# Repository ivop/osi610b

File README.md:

# Ohio Scientific 610B Remake

### Remake of the Ohio Scientific 610B Floppy Controller and Memory Expansion PCB

* The new [schematics](doc/osi610b-schematic.pdf) are based on the original schematics, but with all [errors](doc/errors.txt) fixed.
* The PCB is mostly identical to the original, but with added silkscreen, and jumpers instead of trace cuts.
* Except for drive type selection, which is kept original and does not have a solder mask to facilitate original adjustments.
* Use [ramtest2114](https://github.com/ivop/ramtest2114) to test RAM chips acquired from Ali.

Can be paired with the [Ohio Scientific 600D](https://github.com/ivop/osi600d) "CPU" board.

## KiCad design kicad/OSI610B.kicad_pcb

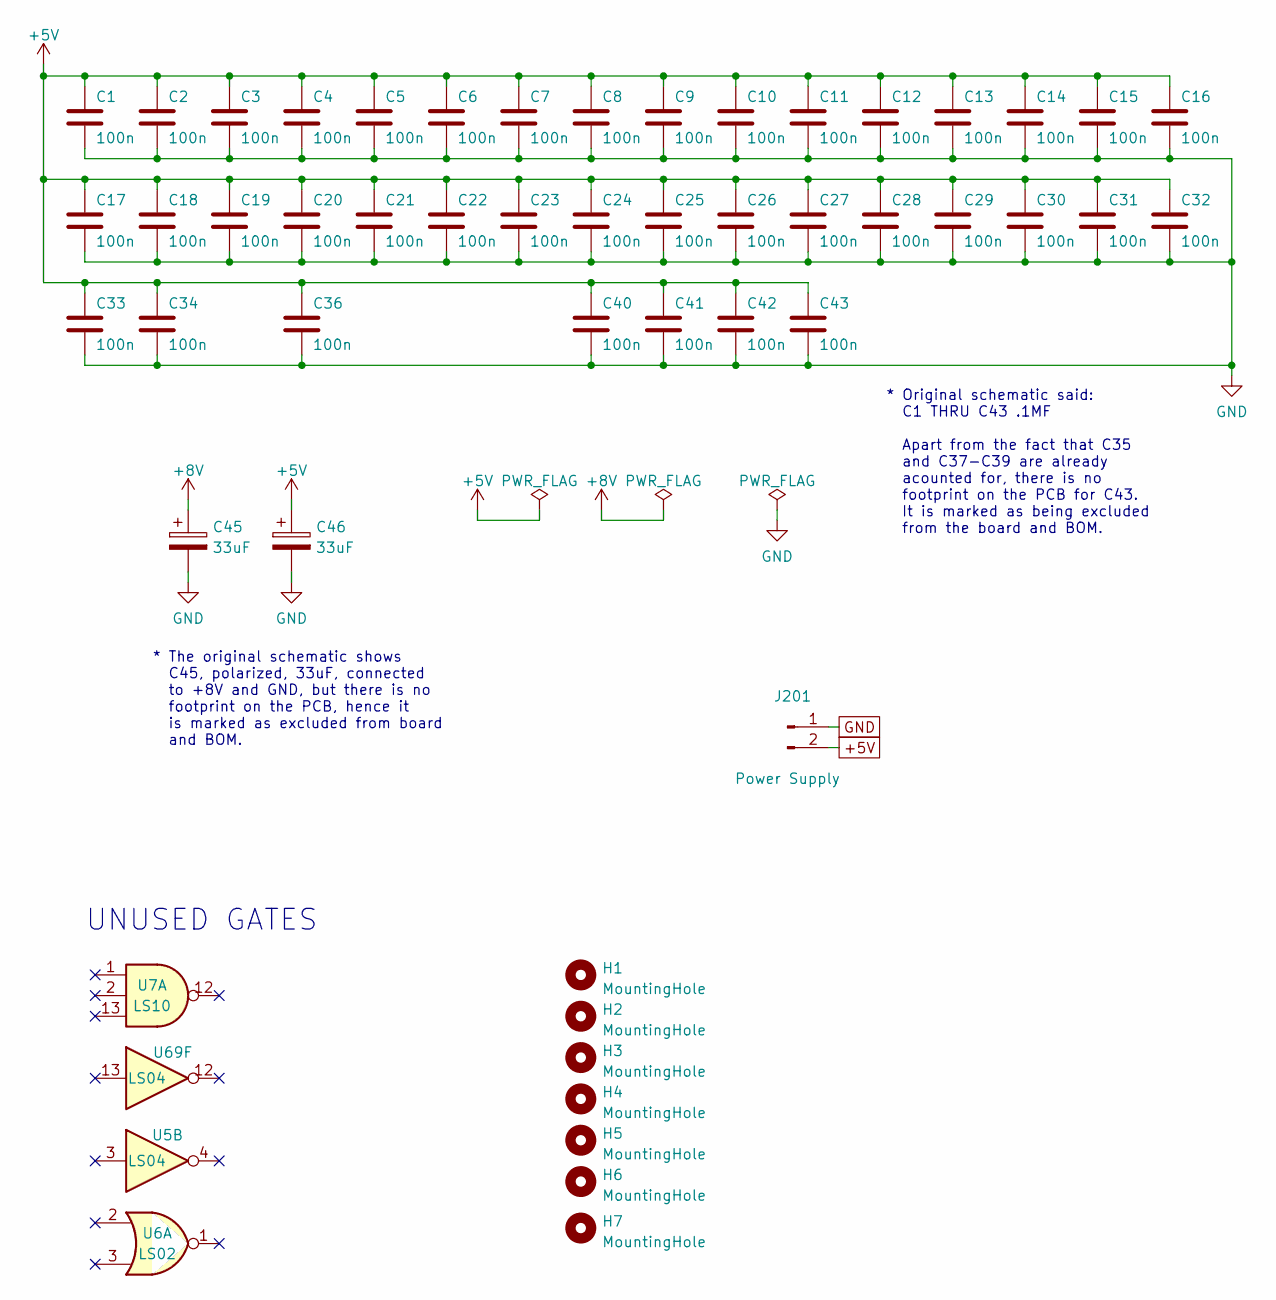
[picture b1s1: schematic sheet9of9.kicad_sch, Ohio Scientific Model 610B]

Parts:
C1, C2, C3, C4, C5, C6, C7, C8, C9, C10, C11, C12, C13, C14, C15, C16, C17, C18, C19, C20, C21, C22, C23, C24, C25, C26, C27, C28, C29, C30, C31, C32, C33, C34, C36, C40, C41, C42, C43: 100n; C_Disc_D4.3mm_W1.9mm_P5.00mm
C45: 33uF
C46: 33uF; CP_Axial_L11.0mm_D6.0mm_P18.00mm_Horizontal
H1, H2, H3, H4, H5: MountingHole; MountingHole_4.3mm_M4_ISO14580
H6, H7: MountingHole; MountingHole_2.7mm_M2.5_ISO14580
J201: Power Supply; Molex_KK-396_A-41791-0002_1x02_P3.96mm_Vertical
U5, U69: LS04; DIP-14_W7.62mm_Socket_LongPads
U6: LS02; DIP-14_W7.62mm_Socket_LongPads
U7: LS10; DIP-14_W7.62mm_Socket_LongPads

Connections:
+5V: C1.1, C2.1, C3.1, C4.1, C5.1, C6.1, C7.1, C8.1, C9.1, C10.1, C11.1, C12.1, C13.1, C14.1, C15.1, C16.1, C17.1, C18.1, C19.1, C20.1, C21.1, C22.1, C23.1, C24.1, C25.1, C26.1, C27.1, C28.1, C29.1, C30.1, C31.1, C32.1, C33.1, C34.1, C36.1, C40.1, C41.1, C42.1, C43.1, C46.1, J201.2; also elsewhere on the board
GND: C1.2, C2.2, C3.2, C4.2, C5.2, C6.2, C7.2, C8.2, C9.2, C10.2, C11.2, C12.2, C13.2, C14.2, C15.2, C16.2, C17.2, C18.2, C19.2, C20.2, C21.2, C22.2, C23.2, C24.2, C25.2, C26.2, C27.2, C28.2, C29.2, C30.2, C31.2, C32.2, C33.2, C34.2, C36.2, C40.2, C41.2, C42.2, C43.2, C45.2, C46.2, J201.1; also elsewhere on the board

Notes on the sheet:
UNUSED GATES
* Original schematic said: C1 THRU C43 .1MF Apart from the fact that C35 and C37-C39 are already acounted for, there is no footprint on the PCB for C43. It is marked as being excluded from the board and BOM.
* The original schematic shows C45, polarized, 33uF, connected to +8V and GND, but there is no footprint on the PCB, hence it is marked as excluded from board and BOM.

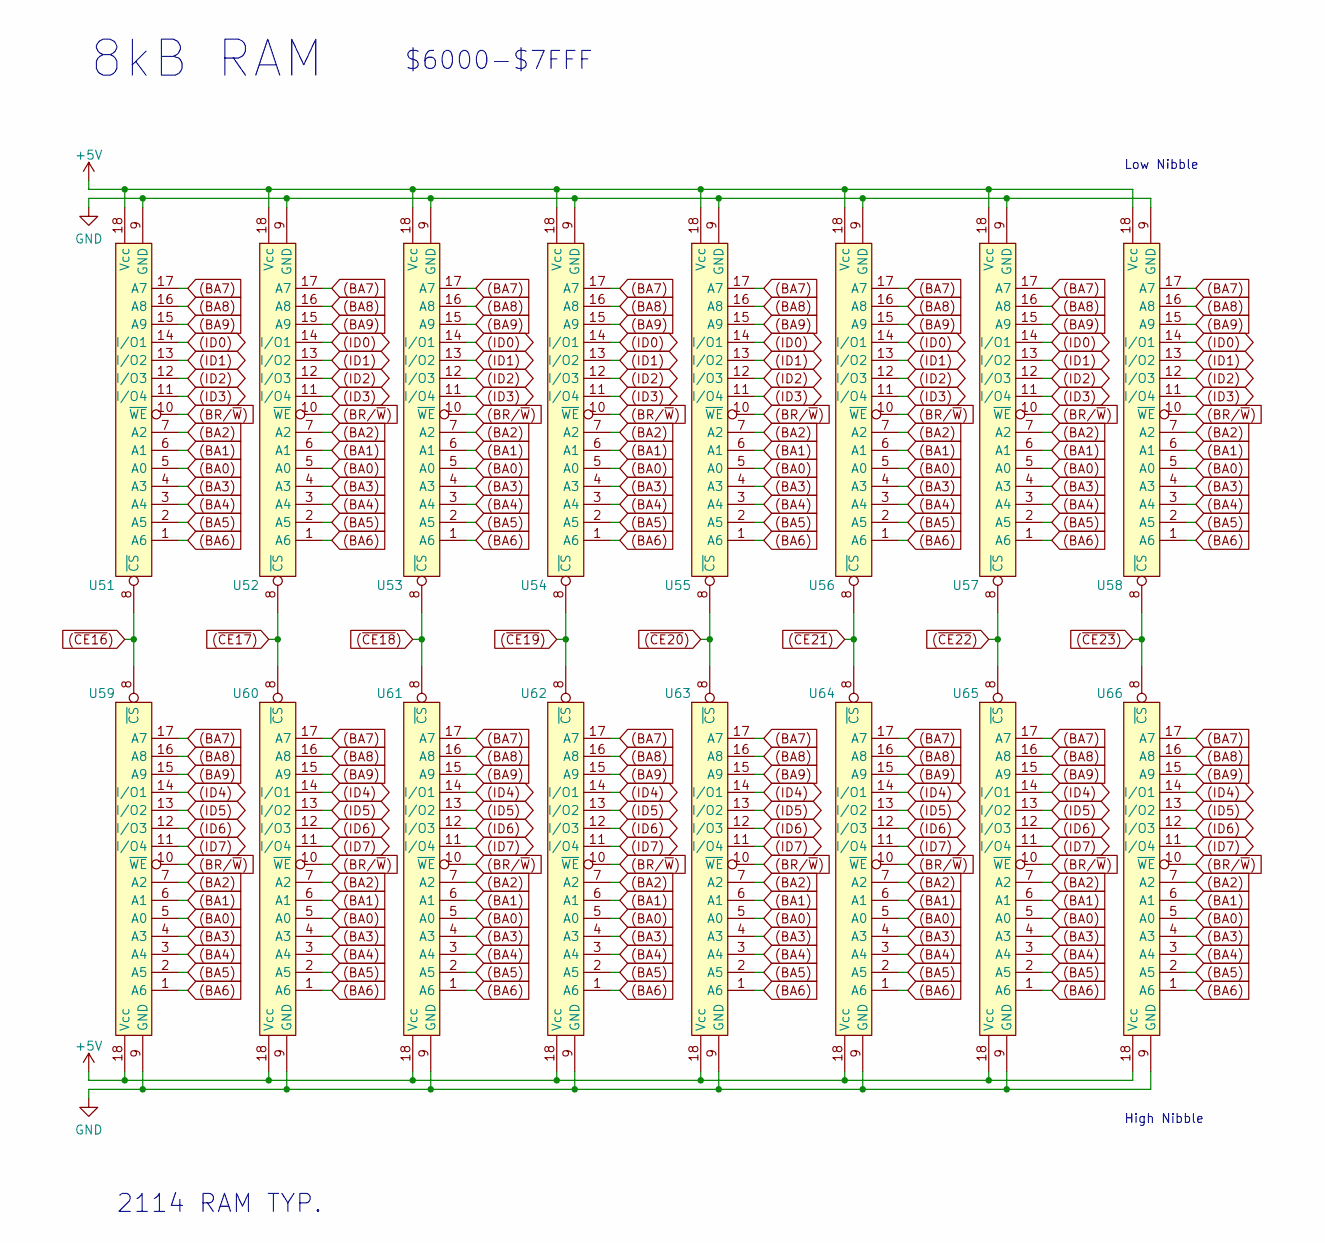
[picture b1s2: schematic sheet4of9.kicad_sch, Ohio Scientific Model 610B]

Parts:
U51, U52, U53, U54, U55, U56, U57, U58: 2114_CS_BOTTOM; DIP-18_W7.62mm_Socket_LongPads
U59, U60, U61, U62, U63, U64, U65, U66: 2114 CS TOP; DIP-18_W7.62mm_Socket_LongPads

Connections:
(BA0): U51.5 (A0), U52.5 (A0), U53.5 (A0), U54.5 (A0), U55.5 (A0), U56.5 (A0), U57.5 (A0), U58.5 (A0), U59.5 (A0), U60.5 (A0), U61.5 (A0), U62.5 (A0), U63.5 (A0), U64.5 (A0), U65.5 (A0), U66.5 (A0); also elsewhere on the board
(BA1): U51.6 (A1), U52.6 (A1), U53.6 (A1), U54.6 (A1), U55.6 (A1), U56.6 (A1), U57.6 (A1), U58.6 (A1), U59.6 (A1), U60.6 (A1), U61.6 (A1), U62.6 (A1), U63.6 (A1), U64.6 (A1), U65.6 (A1), U66.6 (A1); also elsewhere on the board
(BA2): U51.7 (A2), U52.7 (A2), U53.7 (A2), U54.7 (A2), U55.7 (A2), U56.7 (A2), U57.7 (A2), U58.7 (A2), U59.7 (A2), U60.7 (A2), U61.7 (A2), U62.7 (A2), U63.7 (A2), U64.7 (A2), U65.7 (A2), U66.7 (A2); also elsewhere on the board
(BA3): U51.4 (A3), U52.4 (A3), U53.4 (A3), U54.4 (A3), U55.4 (A3), U56.4 (A3), U57.4 (A3), U58.4 (A3), U59.4 (A3), U60.4 (A3), U61.4 (A3), U62.4 (A3), U63.4 (A3), U64.4 (A3), U65.4 (A3), U66.4 (A3); also elsewhere on the board
(BA4): U51.3 (A4), U52.3 (A4), U53.3 (A4), U54.3 (A4), U55.3 (A4), U56.3 (A4), U57.3 (A4), U58.3 (A4), U59.3 (A4), U60.3 (A4), U61.3 (A4), U62.3 (A4), U63.3 (A4), U64.3 (A4), U65.3 (A4), U66.3 (A4); also elsewhere on the board
(BA5): U51.2 (A5), U52.2 (A5), U53.2 (A5), U54.2 (A5), U55.2 (A5), U56.2 (A5), U57.2 (A5), U58.2 (A5), U59.2 (A5), U60.2 (A5), U61.2 (A5), U62.2 (A5), U63.2 (A5), U64.2 (A5), U65.2 (A5), U66.2 (A5); also elsewhere on the board
(BA6): U51.1 (A6), U52.1 (A6), U53.1 (A6), U54.1 (A6), U55.1 (A6), U56.1 (A6), U57.1 (A6), U58.1 (A6), U59.1 (A6), U60.1 (A6), U61.1 (A6), U62.1 (A6), U63.1 (A6), U64.1 (A6), U65.1 (A6), U66.1 (A6); also elsewhere on the board
(BA7): U51.17 (A7), U52.17 (A7), U53.17 (A7), U54.17 (A7), U55.17 (A7), U56.17 (A7), U57.17 (A7), U58.17 (A7), U59.17 (A7), U60.17 (A7), U61.17 (A7), U62.17 (A7), U63.17 (A7), U64.17 (A7), U65.17 (A7), U66.17 (A7); also elsewhere on the board
(BA8): U51.16 (A8), U52.16 (A8), U53.16 (A8), U54.16 (A8), U55.16 (A8), U56.16 (A8), U57.16 (A8), U58.16 (A8), U59.16 (A8), U60.16 (A8), U61.16 (A8), U62.16 (A8), U63.16 (A8), U64.16 (A8), U65.16 (A8), U66.16 (A8); also elsewhere on the board
(BA9): U51.15 (A9), U52.15 (A9), U53.15 (A9), U54.15 (A9), U55.15 (A9), U56.15 (A9), U57.15 (A9), U58.15 (A9), U59.15 (A9), U60.15 (A9), U61.15 (A9), U62.15 (A9), U63.15 (A9), U64.15 (A9), U65.15 (A9), U66.15 (A9); also elsewhere on the board
(BR/~W): U51.10 (~WE), U52.10 (~WE), U53.10 (~WE), U54.10 (~WE), U55.10 (~WE), U56.10 (~WE), U57.10 (~WE), U58.10 (~WE), U59.10 (~WE), U60.10 (~WE), U61.10 (~WE), U62.10 (~WE), U63.10 (~WE), U64.10 (~WE), U65.10 (~WE), U66.10 (~WE); also elsewhere on the board
(ID0): U51.14 (I/O1), U52.14 (I/O1), U53.14 (I/O1), U54.14 (I/O1), U55.14 (I/O1), U56.14 (I/O1), U57.14 (I/O1), U58.14 (I/O1); also elsewhere on the board
(ID1): U51.13 (I/O2), U52.13 (I/O2), U53.13 (I/O2), U54.13 (I/O2), U55.13 (I/O2), U56.13 (I/O2), U57.13 (I/O2), U58.13 (I/O2); also elsewhere on the board
(ID2): U51.12 (I/O3), U52.12 (I/O3), U53.12 (I/O3), U54.12 (I/O3), U55.12 (I/O3), U56.12 (I/O3), U57.12 (I/O3), U58.12 (I/O3); also elsewhere on the board
(ID3): U51.11 (I/O4), U52.11 (I/O4), U53.11 (I/O4), U54.11 (I/O4), U55.11 (I/O4), U56.11 (I/O4), U57.11 (I/O4), U58.11 (I/O4); also elsewhere on the board
(ID4): U59.14 (I/O1), U60.14 (I/O1), U61.14 (I/O1), U62.14 (I/O1), U63.14 (I/O1), U64.14 (I/O1), U65.14 (I/O1), U66.14 (I/O1); also elsewhere on the board
(ID5): U59.13 (I/O2), U60.13 (I/O2), U61.13 (I/O2), U62.13 (I/O2), U63.13 (I/O2), U64.13 (I/O2), U65.13 (I/O2), U66.13 (I/O2); also elsewhere on the board
(ID6): U59.12 (I/O3), U60.12 (I/O3), U61.12 (I/O3), U62.12 (I/O3), U63.12 (I/O3), U64.12 (I/O3), U65.12 (I/O3), U66.12 (I/O3); also elsewhere on the board
(ID7): U59.11 (I/O4), U60.11 (I/O4), U61.11 (I/O4), U62.11 (I/O4), U63.11 (I/O4), U64.11 (I/O4), U65.11 (I/O4), U66.11 (I/O4); also elsewhere on the board
(~CE16): U51.8 (~CS), U59.8 (~CS); also elsewhere on the board
(~CE17): U52.8 (~CS), U60.8 (~CS); also elsewhere on the board
(~CE18): U53.8 (~CS), U61.8 (~CS); also elsewhere on the board
(~CE19): U54.8 (~CS), U62.8 (~CS); also elsewhere on the board
(~CE20): U55.8 (~CS), U63.8 (~CS); also elsewhere on the board
(~CE21): U56.8 (~CS), U64.8 (~CS); also elsewhere on the board
(~CE22): U57.8 (~CS), U65.8 (~CS); also elsewhere on the board
(~CE23): U58.8 (~CS), U66.8 (~CS); also elsewhere on the board
+5V: U51.18 (Vcc), U52.18 (Vcc), U53.18 (Vcc), U54.18 (Vcc), U55.18 (Vcc), U56.18 (Vcc), U57.18 (Vcc), U58.18 (Vcc), U59.18 (Vcc), U60.18 (Vcc), U61.18 (Vcc), U62.18 (Vcc), U63.18 (Vcc), U64.18 (Vcc), U65.18 (Vcc), U66.18 (Vcc); also elsewhere on the board
GND: U51.9 (GND), U52.9 (GND), U53.9 (GND), U54.9 (GND), U55.9 (GND), U56.9 (GND), U57.9 (GND), U58.9 (GND), U59.9 (GND), U60.9 (GND), U61.9 (GND), U62.9 (GND), U63.9 (GND), U64.9 (GND), U65.9 (GND), U66.9 (GND); also elsewhere on the board

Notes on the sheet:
2114 RAM TYP.
8kB RAM
High Nibble
$6000-$7FFF
Low Nibble

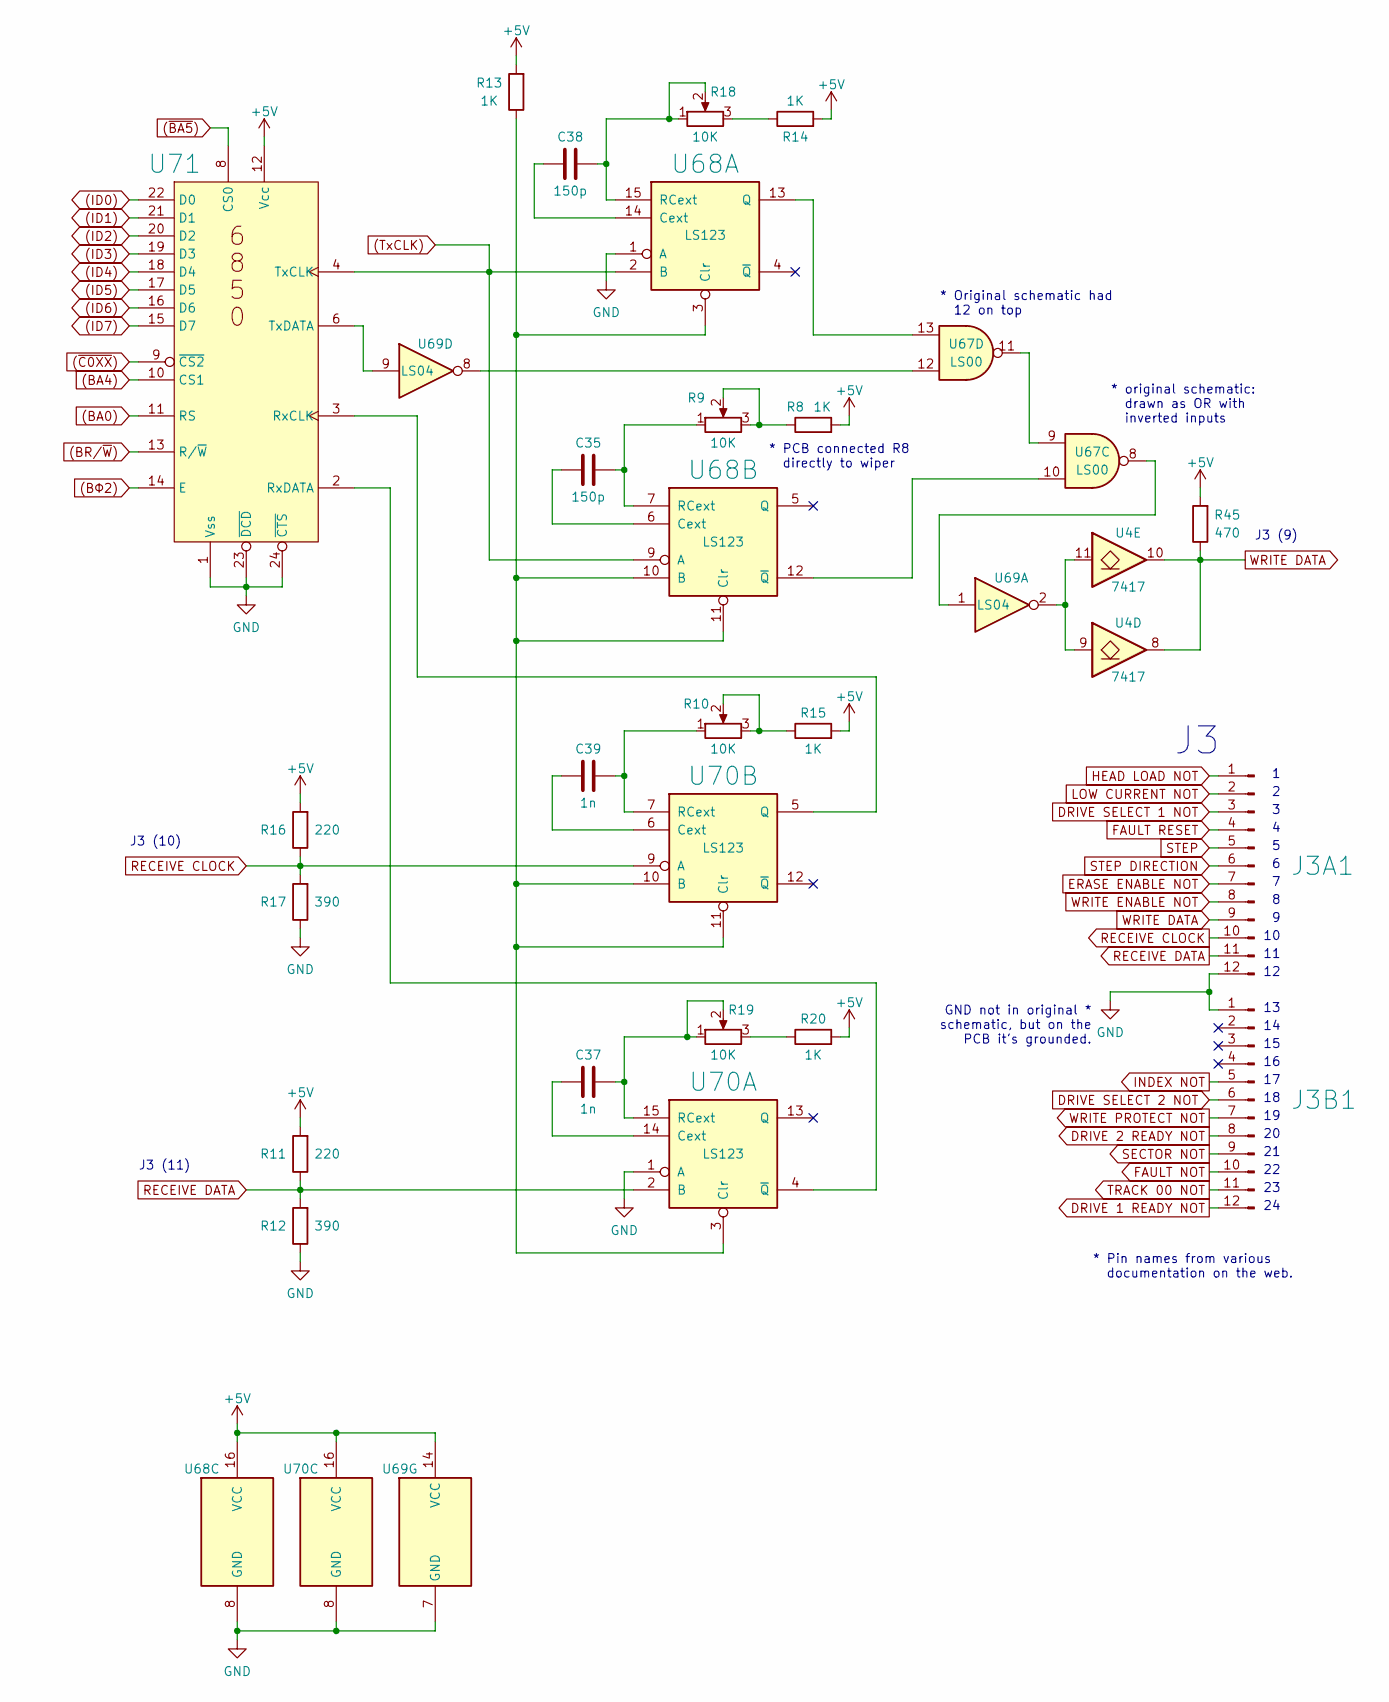
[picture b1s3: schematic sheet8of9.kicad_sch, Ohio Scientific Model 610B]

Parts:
C35, C38: 150p; C_Disc_D4.3mm_W1.9mm_P5.00mm
C37, C39: 1n; C_Disc_D4.3mm_W1.9mm_P5.00mm
J3A1, J3B1: Conn_01x12_Male; Adapted Molex_KK-396_A-41791-0012_1x12_P3.96mm_Vertical
R8, R13, R14, R15, R20: 1K; R_Axial_DIN0309_L9.0mm_D3.2mm_P12.70mm_Horizontal
R9, R10, R18, R19: 10K; Potentiometer_Bourns_3266Y_Vertical
R11, R16: 220; R_Axial_DIN0309_L9.0mm_D3.2mm_P12.70mm_Horizontal
R12, R17: 390; R_Axial_DIN0309_L9.0mm_D3.2mm_P12.70mm_Horizontal
R45: 470; R_Axial_DIN0309_L9.0mm_D3.2mm_P12.70mm_Horizontal
U4: 7417; DIP-14_W7.62mm_Socket_LongPads
U67: LS00; DIP-14_W7.62mm_Socket_LongPads
U68, U70: LS123; DIP-16_W7.62mm_Socket_LongPads
U69: LS04; DIP-14_W7.62mm_Socket_LongPads
U71: 6850; DIP-24_W15.24mm_Socket_LongPads

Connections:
(BA0): U71.11 (RS); also elsewhere on the board
(BA4): U71.10 (CS1); also elsewhere on the board
(BR/~W): U71.13 (R/~W); also elsewhere on the board
(BΦ2): U71.14 (E); also elsewhere on the board
(ID0): U71.22 (D0); also elsewhere on the board
(ID1): U71.21 (D1); also elsewhere on the board
(ID2): U71.20 (D2); also elsewhere on the board
(ID3): U71.19 (D3); also elsewhere on the board
(ID4): U71.18 (D4); also elsewhere on the board
(ID5): U71.17 (D5); also elsewhere on the board
(ID6): U71.16 (D6); also elsewhere on the board
(ID7): U71.15 (D7); also elsewhere on the board
(TxCLK): U68.2 (B), U68.9 (A), U71.4 (TxCLK); also elsewhere on the board
(~BA5): U71.8 (CS0); also elsewhere on the board
(~C0XX): U71.9 (~CS2); also elsewhere on the board
+5V: R8.2, R11.2, R13.2, R14.2, R15.2, R16.2, R20.2, R45.2, U68.16 (VCC), U69.14 (VCC), U70.16 (VCC), U71.12 (Vcc); also elsewhere on the board
DRIVE 1 READY NOT: J3B1.12; also elsewhere on the board
DRIVE 2 READY NOT: J3B1.8; also elsewhere on the board
DRIVE SELECT 1 NOT: J3A1.3; also elsewhere on the board
DRIVE SELECT 2 NOT: J3B1.6; also elsewhere on the board
ERASE ENABLE NOT: J3A1.7; also elsewhere on the board
FAULT NOT: J3B1.10; also elsewhere on the board
FAULT RESET: J3A1.4; also elsewhere on the board
GND: J3A1.12, J3B1.1, R12.1, R17.1, U68.1 (A), U68.8 (GND), U69.7 (GND), U70.1 (A), U70.8 (GND), U71.1 (Vss), U71.23 (~DCD), U71.24 (~CTS); also elsewhere on the board
HEAD LOAD NOT: J3A1.1; also elsewhere on the board
INDEX NOT: J3B1.5; also elsewhere on the board
LOW CURRENT NOT: J3A1.2; also elsewhere on the board
unnamed: C35.1, U68.6 (Cext)
unnamed: C35.2, R9.1, U68.7 (RCext)
unnamed: C37.1, U70.14 (Cext)
unnamed: C37.2, R19.1, R19.2, U70.15 (RCext)
unnamed: C38.1, U68.14 (Cext)
unnamed: C38.2, R18.1, R18.2, U68.15 (RCext)
unnamed: C39.1, U70.6 (Cext)
unnamed: C39.2, R10.1, U70.7 (RCext)
unnamed: R8.1, R9.2, R9.3
unnamed: R10.2, R10.3, R15.1
unnamed: R13.1, U68.3 (Clr), U68.10 (B), U68.11 (Clr), U70.3 (Clr), U70.10 (B), U70.11 (Clr)
unnamed: R14.1, R18.3
unnamed: R19.3, R20.1
unnamed: U4.9 (4A), U4.11 (5A), U69.2
unnamed: U67.8, U69.1
unnamed: U67.10, U68.12 (~Q)
unnamed: U67.9, U67.11
unnamed: U67.12, U69.8
unnamed: U67.13, U68.13 (Q)
unnamed: U69.9, U71.6 (TxDATA)
unnamed: U70.4 (~Q), U71.2 (RxDATA)
unnamed: U70.5 (Q), U71.3 (RxCLK)
RECEIVE CLOCK: J3A1.10, R16.1, R17.2, U70.9 (A)
RECEIVE DATA: J3A1.11, R11.1, R12.2, U70.2 (B)
SECTOR NOT: J3B1.9; also elsewhere on the board
STEP: J3A1.5; also elsewhere on the board
STEP DIRECTION: J3A1.6; also elsewhere on the board
TRACK 00 NOT: J3B1.11; also elsewhere on the board
WRITE DATA: J3A1.9, R45.1, U4.8 (4Y), U4.10 (5Y)
WRITE ENABLE NOT: J3A1.8; also elsewhere on the board
WRITE PROTECT NOT: J3B1.7; also elsewhere on the board

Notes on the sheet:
J3 (10)
GND not in original * schematic, but on the PCB it's grounded.
* Pin names from various documentation on the web.
* original schematic: drawn as OR with inverted inputs
J3 (9)
* PCB connected R8 directly to wiper
* Original schematic had 12 on top
J3 (11)

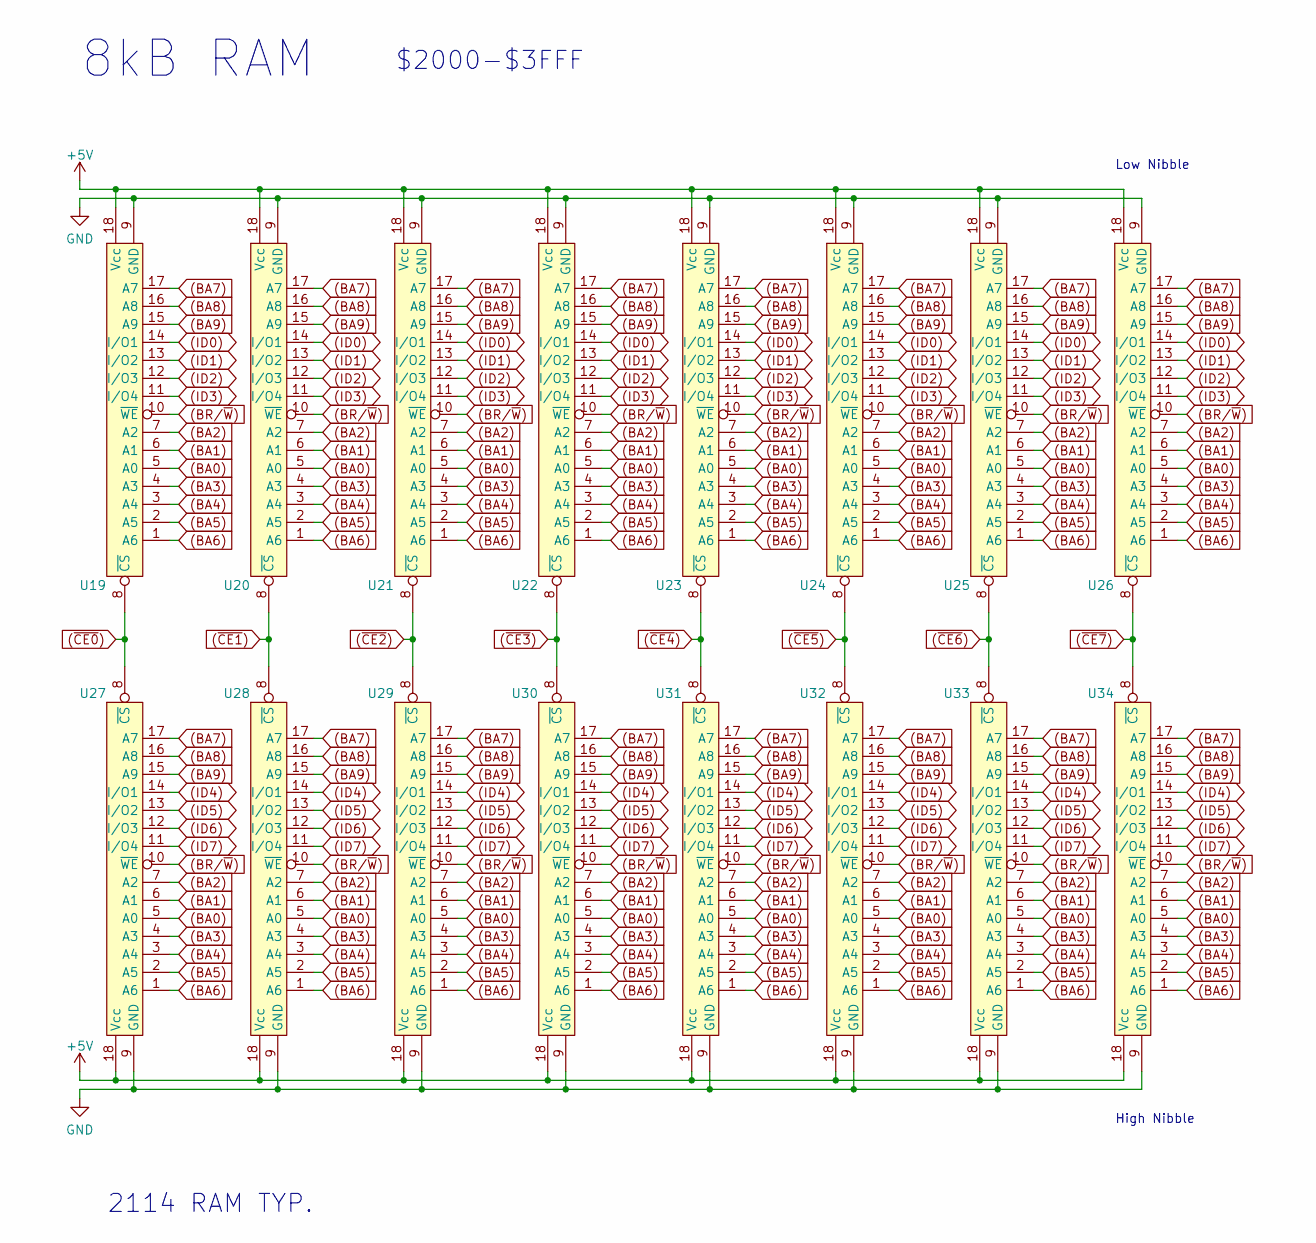
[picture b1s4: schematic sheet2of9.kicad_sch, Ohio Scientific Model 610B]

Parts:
U19, U20, U21, U22, U23, U24, U25, U26: 2114_CS_BOTTOM; DIP-18_W7.62mm_Socket_LongPads
U27, U28, U29, U30, U31, U32, U33, U34: 2114 CS TOP; DIP-18_W7.62mm_Socket_LongPads

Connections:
(BA0): U19.5 (A0), U20.5 (A0), U21.5 (A0), U22.5 (A0), U23.5 (A0), U24.5 (A0), U25.5 (A0), U26.5 (A0), U27.5 (A0), U28.5 (A0), U29.5 (A0), U30.5 (A0), U31.5 (A0), U32.5 (A0), U33.5 (A0), U34.5 (A0); also elsewhere on the board
(BA1): U19.6 (A1), U20.6 (A1), U21.6 (A1), U22.6 (A1), U23.6 (A1), U24.6 (A1), U25.6 (A1), U26.6 (A1), U27.6 (A1), U28.6 (A1), U29.6 (A1), U30.6 (A1), U31.6 (A1), U32.6 (A1), U33.6 (A1), U34.6 (A1); also elsewhere on the board
(BA2): U19.7 (A2), U20.7 (A2), U21.7 (A2), U22.7 (A2), U23.7 (A2), U24.7 (A2), U25.7 (A2), U26.7 (A2), U27.7 (A2), U28.7 (A2), U29.7 (A2), U30.7 (A2), U31.7 (A2), U32.7 (A2), U33.7 (A2), U34.7 (A2); also elsewhere on the board
(BA3): U19.4 (A3), U20.4 (A3), U21.4 (A3), U22.4 (A3), U23.4 (A3), U24.4 (A3), U25.4 (A3), U26.4 (A3), U27.4 (A3), U28.4 (A3), U29.4 (A3), U30.4 (A3), U31.4 (A3), U32.4 (A3), U33.4 (A3), U34.4 (A3); also elsewhere on the board
(BA4): U19.3 (A4), U20.3 (A4), U21.3 (A4), U22.3 (A4), U23.3 (A4), U24.3 (A4), U25.3 (A4), U26.3 (A4), U27.3 (A4), U28.3 (A4), U29.3 (A4), U30.3 (A4), U31.3 (A4), U32.3 (A4), U33.3 (A4), U34.3 (A4); also elsewhere on the board
(BA5): U19.2 (A5), U20.2 (A5), U21.2 (A5), U22.2 (A5), U23.2 (A5), U24.2 (A5), U25.2 (A5), U26.2 (A5), U27.2 (A5), U28.2 (A5), U29.2 (A5), U30.2 (A5), U31.2 (A5), U32.2 (A5), U33.2 (A5), U34.2 (A5); also elsewhere on the board
(BA6): U19.1 (A6), U20.1 (A6), U21.1 (A6), U22.1 (A6), U23.1 (A6), U24.1 (A6), U25.1 (A6), U26.1 (A6), U27.1 (A6), U28.1 (A6), U29.1 (A6), U30.1 (A6), U31.1 (A6), U32.1 (A6), U33.1 (A6), U34.1 (A6); also elsewhere on the board
(BA7): U19.17 (A7), U20.17 (A7), U21.17 (A7), U22.17 (A7), U23.17 (A7), U24.17 (A7), U25.17 (A7), U26.17 (A7), U27.17 (A7), U28.17 (A7), U29.17 (A7), U30.17 (A7), U31.17 (A7), U32.17 (A7), U33.17 (A7), U34.17 (A7); also elsewhere on the board
(BA8): U19.16 (A8), U20.16 (A8), U21.16 (A8), U22.16 (A8), U23.16 (A8), U24.16 (A8), U25.16 (A8), U26.16 (A8), U27.16 (A8), U28.16 (A8), U29.16 (A8), U30.16 (A8), U31.16 (A8), U32.16 (A8), U33.16 (A8), U34.16 (A8); also elsewhere on the board
(BA9): U19.15 (A9), U20.15 (A9), U21.15 (A9), U22.15 (A9), U23.15 (A9), U24.15 (A9), U25.15 (A9), U26.15 (A9), U27.15 (A9), U28.15 (A9), U29.15 (A9), U30.15 (A9), U31.15 (A9), U32.15 (A9), U33.15 (A9), U34.15 (A9); also elsewhere on the board
(BR/~W): U19.10 (~WE), U20.10 (~WE), U21.10 (~WE), U22.10 (~WE), U23.10 (~WE), U24.10 (~WE), U25.10 (~WE), U26.10 (~WE), U27.10 (~WE), U28.10 (~WE), U29.10 (~WE), U30.10 (~WE), U31.10 (~WE), U32.10 (~WE), U33.10 (~WE), U34.10 (~WE); also elsewhere on the board
(ID0): U19.14 (I/O1), U20.14 (I/O1), U21.14 (I/O1), U22.14 (I/O1), U23.14 (I/O1), U24.14 (I/O1), U25.14 (I/O1), U26.14 (I/O1); also elsewhere on the board
(ID1): U19.13 (I/O2), U20.13 (I/O2), U21.13 (I/O2), U22.13 (I/O2), U23.13 (I/O2), U24.13 (I/O2), U25.13 (I/O2), U26.13 (I/O2); also elsewhere on the board
(ID2): U19.12 (I/O3), U20.12 (I/O3), U21.12 (I/O3), U22.12 (I/O3), U23.12 (I/O3), U24.12 (I/O3), U25.12 (I/O3), U26.12 (I/O3); also elsewhere on the board
(ID3): U19.11 (I/O4), U20.11 (I/O4), U21.11 (I/O4), U22.11 (I/O4), U23.11 (I/O4), U24.11 (I/O4), U25.11 (I/O4), U26.11 (I/O4); also elsewhere on the board
(ID4): U27.14 (I/O1), U28.14 (I/O1), U29.14 (I/O1), U30.14 (I/O1), U31.14 (I/O1), U32.14 (I/O1), U33.14 (I/O1), U34.14 (I/O1); also elsewhere on the board
(ID5): U27.13 (I/O2), U28.13 (I/O2), U29.13 (I/O2), U30.13 (I/O2), U31.13 (I/O2), U32.13 (I/O2), U33.13 (I/O2), U34.13 (I/O2); also elsewhere on the board
(ID6): U27.12 (I/O3), U28.12 (I/O3), U29.12 (I/O3), U30.12 (I/O3), U31.12 (I/O3), U32.12 (I/O3), U33.12 (I/O3), U34.12 (I/O3); also elsewhere on the board
(ID7): U27.11 (I/O4), U28.11 (I/O4), U29.11 (I/O4), U30.11 (I/O4), U31.11 (I/O4), U32.11 (I/O4), U33.11 (I/O4), U34.11 (I/O4); also elsewhere on the board
(~CE0): U19.8 (~CS), U27.8 (~CS); also elsewhere on the board
(~CE1): U20.8 (~CS), U28.8 (~CS); also elsewhere on the board
(~CE2): U21.8 (~CS), U29.8 (~CS); also elsewhere on the board
(~CE3): U22.8 (~CS), U30.8 (~CS); also elsewhere on the board
(~CE4): U23.8 (~CS), U31.8 (~CS); also elsewhere on the board
(~CE5): U24.8 (~CS), U32.8 (~CS); also elsewhere on the board
(~CE6): U25.8 (~CS), U33.8 (~CS); also elsewhere on the board
(~CE7): U26.8 (~CS), U34.8 (~CS); also elsewhere on the board
+5V: U19.18 (Vcc), U20.18 (Vcc), U21.18 (Vcc), U22.18 (Vcc), U23.18 (Vcc), U24.18 (Vcc), U25.18 (Vcc), U26.18 (Vcc), U27.18 (Vcc), U28.18 (Vcc), U29.18 (Vcc), U30.18 (Vcc), U31.18 (Vcc), U32.18 (Vcc), U33.18 (Vcc), U34.18 (Vcc); also elsewhere on the board
GND: U19.9 (GND), U20.9 (GND), U21.9 (GND), U22.9 (GND), U23.9 (GND), U24.9 (GND), U25.9 (GND), U26.9 (GND), U27.9 (GND), U28.9 (GND), U29.9 (GND), U30.9 (GND), U31.9 (GND), U32.9 (GND), U33.9 (GND), U34.9 (GND); also elsewhere on the board

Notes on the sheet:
$2000-$3FFF
High Nibble
8kB RAM
Low Nibble
2114 RAM TYP.

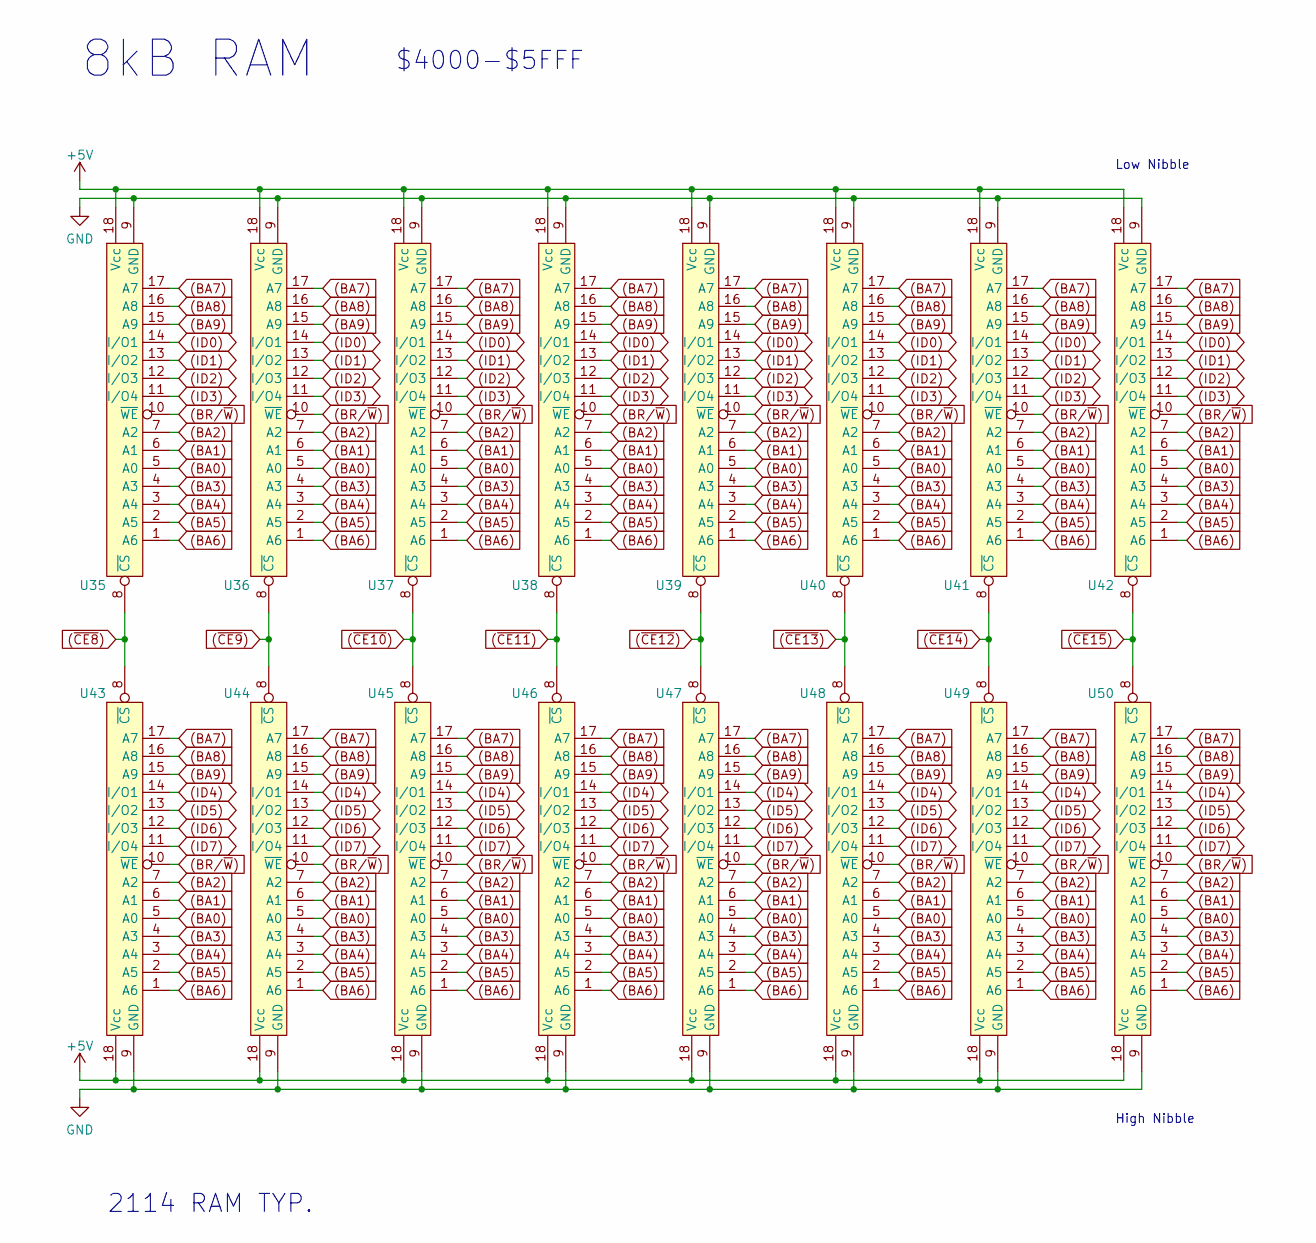
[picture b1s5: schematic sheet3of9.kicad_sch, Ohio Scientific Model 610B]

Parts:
U35, U36, U37, U38, U39, U40, U41, U42: 2114_CS_BOTTOM; DIP-18_W7.62mm_Socket_LongPads
U43, U44, U45, U46, U47, U48, U49, U50: 2114 CS TOP; DIP-18_W7.62mm_Socket_LongPads

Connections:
(BA0): U35.5 (A0), U36.5 (A0), U37.5 (A0), U38.5 (A0), U39.5 (A0), U40.5 (A0), U41.5 (A0), U42.5 (A0), U43.5 (A0), U44.5 (A0), U45.5 (A0), U46.5 (A0), U47.5 (A0), U48.5 (A0), U49.5 (A0), U50.5 (A0); also elsewhere on the board
(BA1): U35.6 (A1), U36.6 (A1), U37.6 (A1), U38.6 (A1), U39.6 (A1), U40.6 (A1), U41.6 (A1), U42.6 (A1), U43.6 (A1), U44.6 (A1), U45.6 (A1), U46.6 (A1), U47.6 (A1), U48.6 (A1), U49.6 (A1), U50.6 (A1); also elsewhere on the board
(BA2): U35.7 (A2), U36.7 (A2), U37.7 (A2), U38.7 (A2), U39.7 (A2), U40.7 (A2), U41.7 (A2), U42.7 (A2), U43.7 (A2), U44.7 (A2), U45.7 (A2), U46.7 (A2), U47.7 (A2), U48.7 (A2), U49.7 (A2), U50.7 (A2); also elsewhere on the board
(BA3): U35.4 (A3), U36.4 (A3), U37.4 (A3), U38.4 (A3), U39.4 (A3), U40.4 (A3), U41.4 (A3), U42.4 (A3), U43.4 (A3), U44.4 (A3), U45.4 (A3), U46.4 (A3), U47.4 (A3), U48.4 (A3), U49.4 (A3), U50.4 (A3); also elsewhere on the board
(BA4): U35.3 (A4), U36.3 (A4), U37.3 (A4), U38.3 (A4), U39.3 (A4), U40.3 (A4), U41.3 (A4), U42.3 (A4), U43.3 (A4), U44.3 (A4), U45.3 (A4), U46.3 (A4), U47.3 (A4), U48.3 (A4), U49.3 (A4), U50.3 (A4); also elsewhere on the board
(BA5): U35.2 (A5), U36.2 (A5), U37.2 (A5), U38.2 (A5), U39.2 (A5), U40.2 (A5), U41.2 (A5), U42.2 (A5), U43.2 (A5), U44.2 (A5), U45.2 (A5), U46.2 (A5), U47.2 (A5), U48.2 (A5), U49.2 (A5), U50.2 (A5); also elsewhere on the board
(BA6): U35.1 (A6), U36.1 (A6), U37.1 (A6), U38.1 (A6), U39.1 (A6), U40.1 (A6), U41.1 (A6), U42.1 (A6), U43.1 (A6), U44.1 (A6), U45.1 (A6), U46.1 (A6), U47.1 (A6), U48.1 (A6), U49.1 (A6), U50.1 (A6); also elsewhere on the board
(BA7): U35.17 (A7), U36.17 (A7), U37.17 (A7), U38.17 (A7), U39.17 (A7), U40.17 (A7), U41.17 (A7), U42.17 (A7), U43.17 (A7), U44.17 (A7), U45.17 (A7), U46.17 (A7), U47.17 (A7), U48.17 (A7), U49.17 (A7), U50.17 (A7); also elsewhere on the board
(BA8): U35.16 (A8), U36.16 (A8), U37.16 (A8), U38.16 (A8), U39.16 (A8), U40.16 (A8), U41.16 (A8), U42.16 (A8), U43.16 (A8), U44.16 (A8), U45.16 (A8), U46.16 (A8), U47.16 (A8), U48.16 (A8), U49.16 (A8), U50.16 (A8); also elsewhere on the board
(BA9): U35.15 (A9), U36.15 (A9), U37.15 (A9), U38.15 (A9), U39.15 (A9), U40.15 (A9), U41.15 (A9), U42.15 (A9), U43.15 (A9), U44.15 (A9), U45.15 (A9), U46.15 (A9), U47.15 (A9), U48.15 (A9), U49.15 (A9), U50.15 (A9); also elsewhere on the board
(BR/~W): U35.10 (~WE), U36.10 (~WE), U37.10 (~WE), U38.10 (~WE), U39.10 (~WE), U40.10 (~WE), U41.10 (~WE), U42.10 (~WE), U43.10 (~WE), U44.10 (~WE), U45.10 (~WE), U46.10 (~WE), U47.10 (~WE), U48.10 (~WE), U49.10 (~WE), U50.10 (~WE); also elsewhere on the board
(ID0): U35.14 (I/O1), U36.14 (I/O1), U37.14 (I/O1), U38.14 (I/O1), U39.14 (I/O1), U40.14 (I/O1), U41.14 (I/O1), U42.14 (I/O1); also elsewhere on the board
(ID1): U35.13 (I/O2), U36.13 (I/O2), U37.13 (I/O2), U38.13 (I/O2), U39.13 (I/O2), U40.13 (I/O2), U41.13 (I/O2), U42.13 (I/O2); also elsewhere on the board
(ID2): U35.12 (I/O3), U36.12 (I/O3), U37.12 (I/O3), U38.12 (I/O3), U39.12 (I/O3), U40.12 (I/O3), U41.12 (I/O3), U42.12 (I/O3); also elsewhere on the board
(ID3): U35.11 (I/O4), U36.11 (I/O4), U37.11 (I/O4), U38.11 (I/O4), U39.11 (I/O4), U40.11 (I/O4), U41.11 (I/O4), U42.11 (I/O4); also elsewhere on the board
(ID4): U43.14 (I/O1), U44.14 (I/O1), U45.14 (I/O1), U46.14 (I/O1), U47.14 (I/O1), U48.14 (I/O1), U49.14 (I/O1), U50.14 (I/O1); also elsewhere on the board
(ID5): U43.13 (I/O2), U44.13 (I/O2), U45.13 (I/O2), U46.13 (I/O2), U47.13 (I/O2), U48.13 (I/O2), U49.13 (I/O2), U50.13 (I/O2); also elsewhere on the board
(ID6): U43.12 (I/O3), U44.12 (I/O3), U45.12 (I/O3), U46.12 (I/O3), U47.12 (I/O3), U48.12 (I/O3), U49.12 (I/O3), U50.12 (I/O3); also elsewhere on the board
(ID7): U43.11 (I/O4), U44.11 (I/O4), U45.11 (I/O4), U46.11 (I/O4), U47.11 (I/O4), U48.11 (I/O4), U49.11 (I/O4), U50.11 (I/O4); also elsewhere on the board
(~CE8): U35.8 (~CS), U43.8 (~CS); also elsewhere on the board
(~CE9): U36.8 (~CS), U44.8 (~CS); also elsewhere on the board
(~CE10): U37.8 (~CS), U45.8 (~CS); also elsewhere on the board
(~CE11): U38.8 (~CS), U46.8 (~CS); also elsewhere on the board
(~CE12): U39.8 (~CS), U47.8 (~CS); also elsewhere on the board
(~CE13): U40.8 (~CS), U48.8 (~CS); also elsewhere on the board
(~CE14): U41.8 (~CS), U49.8 (~CS); also elsewhere on the board
(~CE15): U42.8 (~CS), U50.8 (~CS); also elsewhere on the board
+5V: U35.18 (Vcc), U36.18 (Vcc), U37.18 (Vcc), U38.18 (Vcc), U39.18 (Vcc), U40.18 (Vcc), U41.18 (Vcc), U42.18 (Vcc), U43.18 (Vcc), U44.18 (Vcc), U45.18 (Vcc), U46.18 (Vcc), U47.18 (Vcc), U48.18 (Vcc), U49.18 (Vcc), U50.18 (Vcc); also elsewhere on the board
GND: U35.9 (GND), U36.9 (GND), U37.9 (GND), U38.9 (GND), U39.9 (GND), U40.9 (GND), U41.9 (GND), U42.9 (GND), U43.9 (GND), U44.9 (GND), U45.9 (GND), U46.9 (GND), U47.9 (GND), U48.9 (GND), U49.9 (GND), U50.9 (GND); also elsewhere on the board

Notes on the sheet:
8kB RAM
$4000-$5FFF
Low Nibble
2114 RAM TYP.
High Nibble
